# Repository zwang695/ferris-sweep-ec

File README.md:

# Ferris Sweep EC

An open, 34-key (`3x5+2` per half) Topre electrocapacitive split keyboard using
Ferris Sweep-style geometry and the known-built Tako Rev1 sensing architecture.

## Tooling

KiCad 10.0.5 is installed through Flatpak. Use `./scripts/kicad-cli` for
schematic ERC, PCB DRC, exports, and renders. QMK CLI 1.2.0 is also available;
firmware is kept reproducible in this repository rather than depending on the
machine's existing QMK checkout.

This repository is an engineering project. Files under `production/` are not
released for fabrication until every check in `docs/verification-plan.md` has
passed and the release is explicitly tagged as a prototype.

## Revision A goals

- Functional wired electrocapacitive keyboard.
- Separate, non-reversible left and right PCBs.
- 19.05 mm nominal key pitch with Sweep-style column stagger.
- 17 keys per half: three rows of five plus two thumb keys.
- Socketable Pro-Micro-pin-compatible RP2040 controller and local EC sensing
  front end on each half.
- QMK firmware with raw ADC diagnostics for post-assembly threshold tuning.
- USB-C on both halves for flashing and independent bring-up.
- Wired serial split transport.
- No RGB, display, encoder, wireless, or Vial in Revision A.

## Repository layout

- `docs/` — requirements, decisions, reference audit, and verification plan.
- `hardware/` — KiCad project and project-local libraries.
- `mechanical/` — layout coordinates, plate, and compression-stack files.
- `firmware/` — QMK keyboard implementation and keymaps.
- `simulation/` — analog-front-end models and ADC stimulus traces.
- `tests/` — schematic, PCB, firmware, and generated-output checks.
- `references/` — pinned upstream metadata; third-party files retain their
  original licenses and are not copied here until their provenance is clear.
- `production/` — generated Gerbers, drills, BOM, and placement files.

## Status

Controller PCB, Topre plate, bottom plate, and upstream-QMK firmware now pass
the automated pre-fabrication checks. The project remains a prototype: static
checks and behavioral models cannot replace calibration with real domes,
springs, housings, and fabricated sensor electrodes.

Run `./scripts/check-all` for the complete automated gate. See
`docs/tooling.md`, `docs/verification-status.md`, `docs/bom.md`, and
`docs/bring-up.md` for setup, evidence, parts, and physical validation. The
Tako/Cipulot comparison is in `docs/ec-cross-check.md`.

For the wired JLCPCB fabrication and assembly package, run
`./scripts/generate-jlcpcb` and follow `production/jlcpcb/README.md`.

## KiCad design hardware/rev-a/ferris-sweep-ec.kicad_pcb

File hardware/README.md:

# Hardware

`rev-a/` contains the active KiCad 10 design. It starts as a mechanically
imported, renamed copy of the pinned MIT-licensed Tako Rev1 source. The import
is reproducible with `scripts/import-tako-rev1`; subsequent changes are made in
the active source and reviewed against the imported baseline.

The upstream project commit and all other references are pinned in
`references/reference-audit.md`. The original MIT text is retained as
`hardware/LICENSE.tako.MIT`.

The project-level ERC, DRC, firmware, and mechanical gates in
`docs/verification-plan.md` now pass. Revision A is suitable for an informed
prototype review; physical Topre signal margin remains unproven until a real
dome, spring, housing, and fabricated sensor stack are measured.

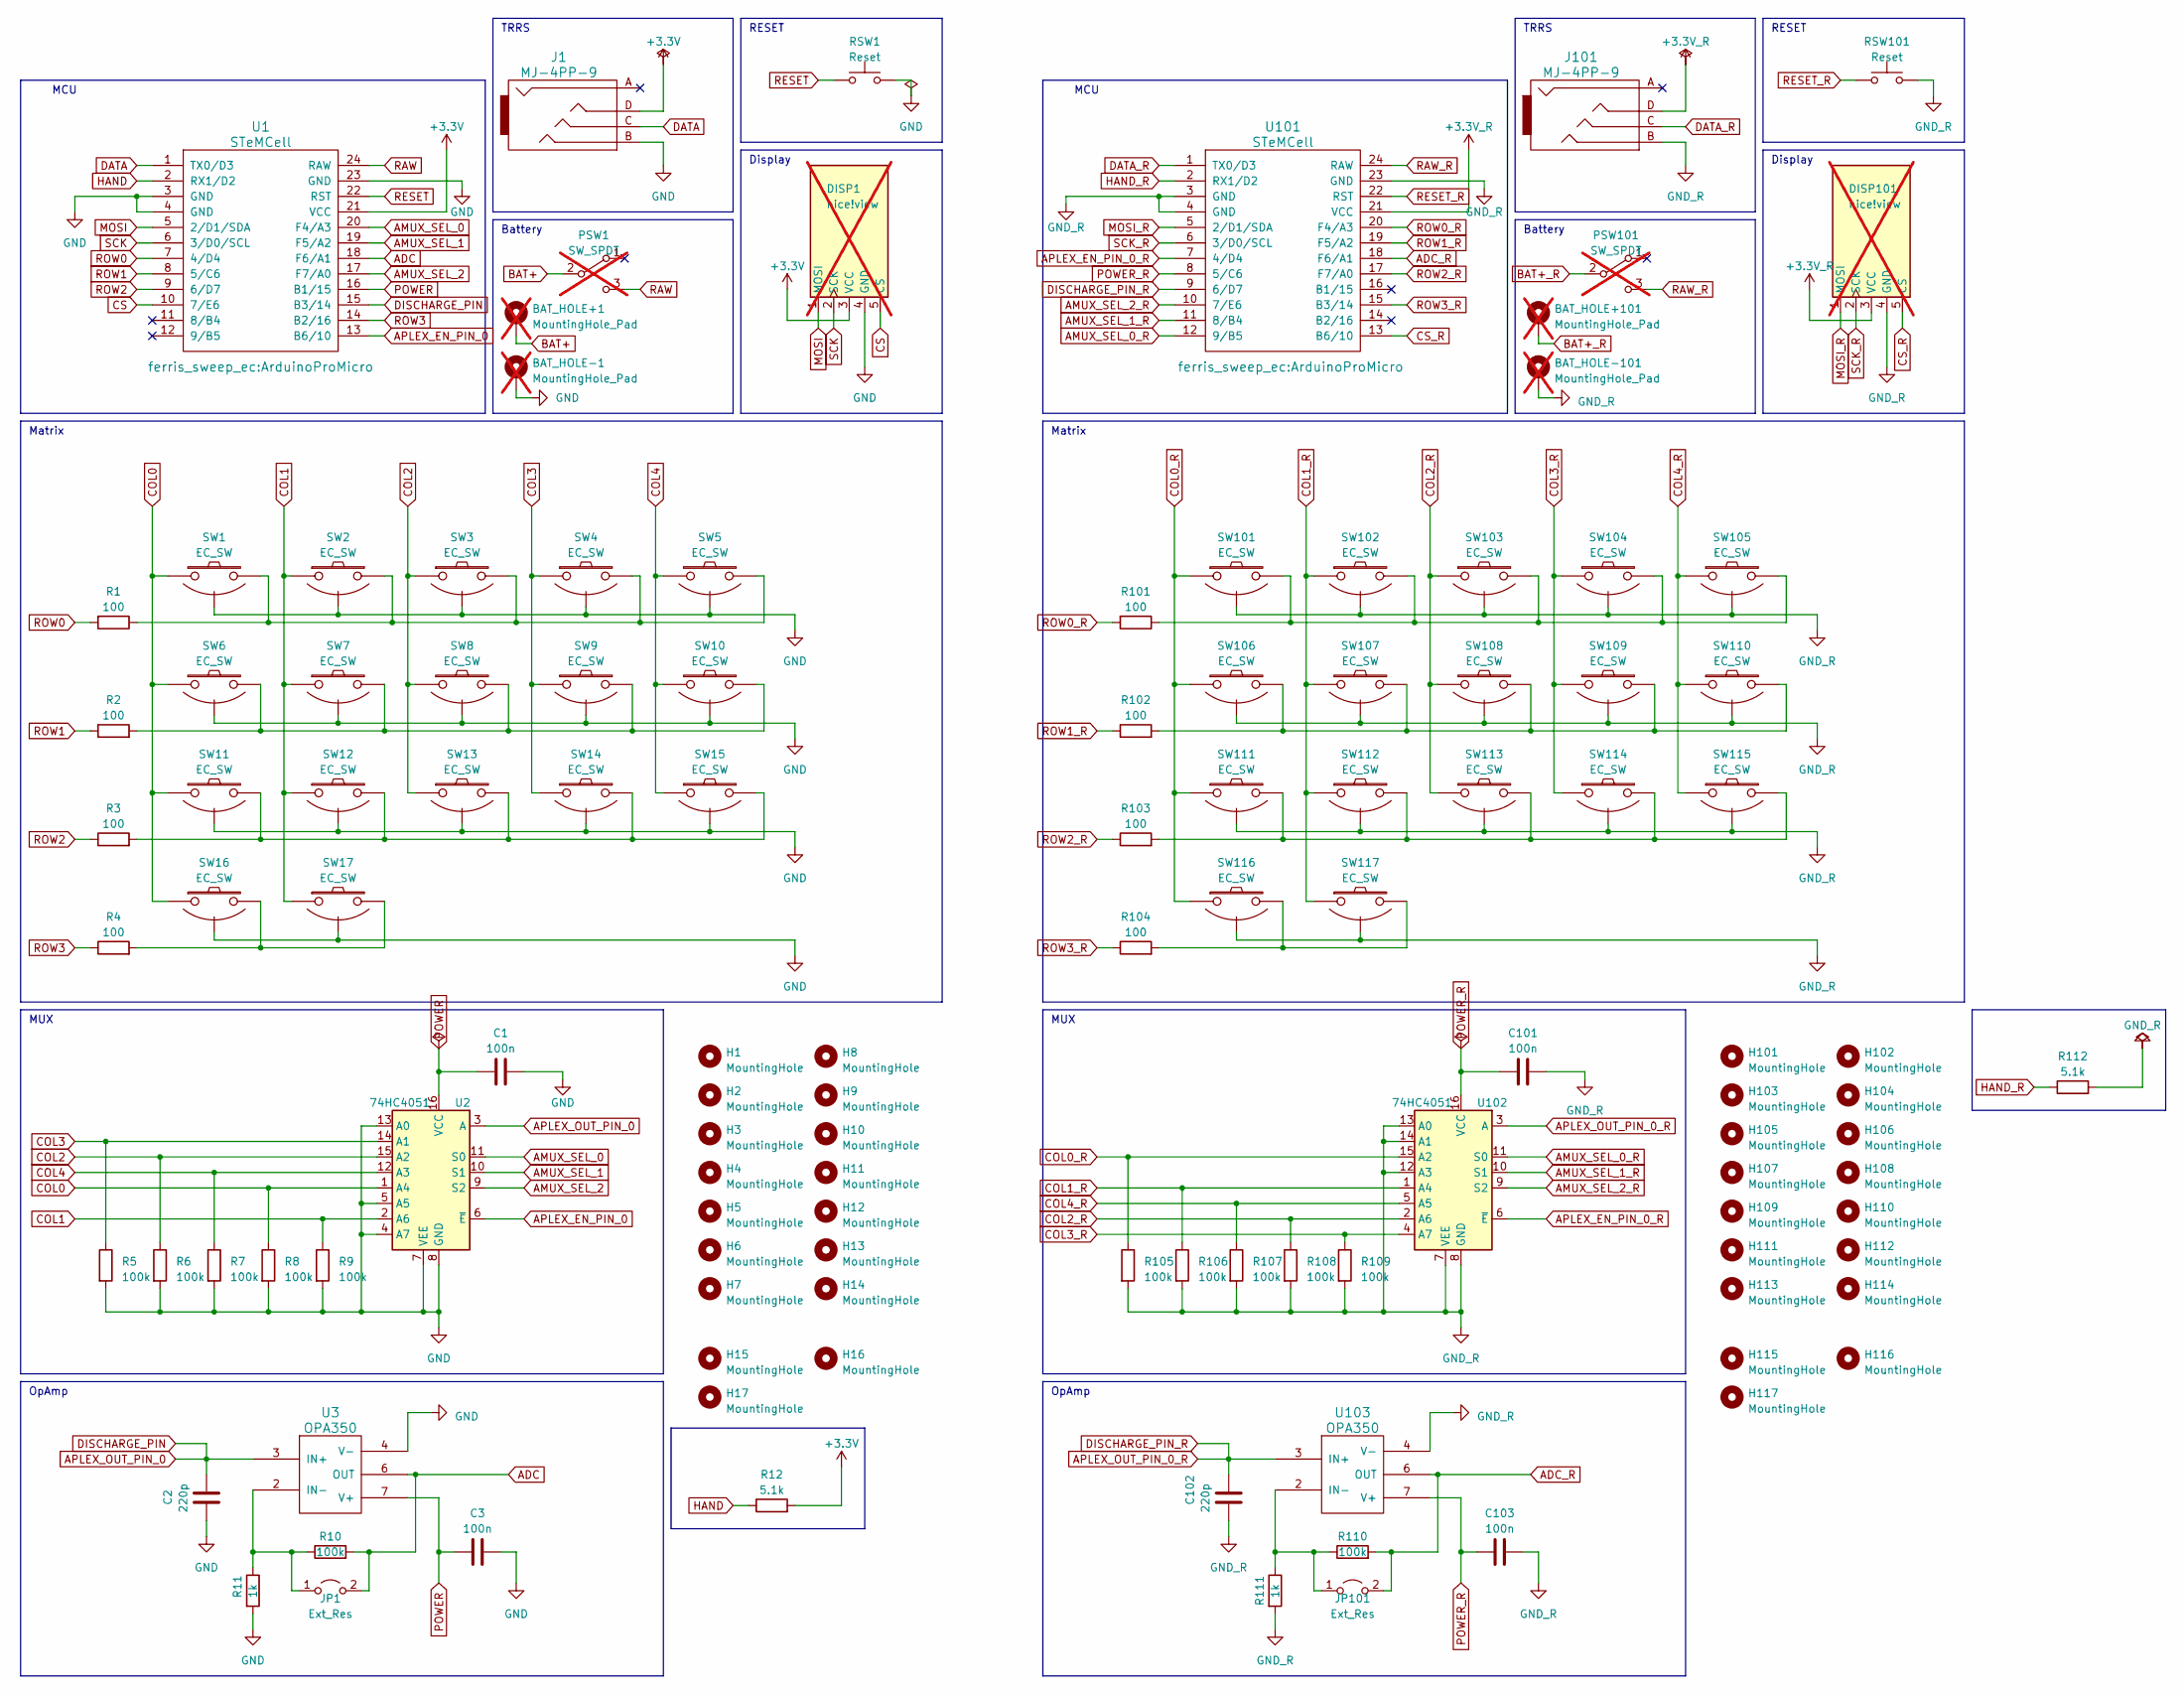
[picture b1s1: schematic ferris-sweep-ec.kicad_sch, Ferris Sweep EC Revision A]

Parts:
BAT_HOLE+1, BAT_HOLE+101: MountingHole_Pad; bat_pin+; not fitted
BAT_HOLE-1, BAT_HOLE-101: MountingHole_Pad; bat_pin-; not fitted
C1, C3, C101, C103: 100n; C_0805_2012Metric_Pad1.18x1.45mm_HandSolder
C2, C102: 220p; C_0805_2012Metric_Pad1.18x1.45mm_HandSolder
DISP1, DISP101: nice!view; nice_view; not fitted
H1, H2, H3, H4, H5, H6, H7, H8, H9, H10, H11, H12, H13, H14, H101, H102, H103, H104, H105, H106, H107, H108, H109, H110, H111, H112, H113, H114: MountingHole; MountingHole_3.4mm
H15, H16, H17, H115, H116, H117: MountingHole; M2_hole_3.5mm
J1, J101: MJ-4PP-9; TRRS-PJ-320A
JP1, JP101: Ext_Res; R_0805_2012Metric_Pad1.20x1.40mm_HandSolder
PSW1, PSW101: SW_SPDT; SW_SPDT_SMD_PCM12; not fitted
R1, R2, R3, R4, R101, R102, R103, R104: 100; R_0805_2012Metric_Pad1.20x1.40mm_HandSolder
R5, R6, R7, R8, R9, R10, R105, R106, R107, R108, R109, R110: 100k; R_0805_2012Metric_Pad1.20x1.40mm_HandSolder
R11, R111: 1k; R_0805_2012Metric_Pad1.20x1.40mm_HandSolder
R12, R112: 5.1k; R_0805_2012Metric_Pad1.20x1.40mm_HandSolder
RSW1, RSW101: Reset; Panasonic_EVQPUL_EVQPUC
SW1, SW2, SW3, SW4, SW5, SW6, SW7, SW8, SW9, SW10, SW11, SW12, SW13, SW14, SW15, SW101, SW102, SW103, SW104, SW105, SW106, SW107, SW108, SW109, SW110, SW111, SW112, SW113, SW114, SW115: EC_SW; ecs_pad_1U_no_ring
SW16, SW17, SW116, SW117: EC_SW; ecs_pad_1U_no_ring_90deg
U1, U101: STeMCell; ArduinoProMicro
U2, U102: 74HC4051; SOIC-16_3.9x9.9mm_P1.27mm
U3, U103: OPA350; SOIC-8_3.9x4.9mm_P1.27mm

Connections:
+3.3V: DISP1.3 (VCC), J1.D, R12.2, U1.21 (VCC)
+3.3V_R: DISP101.3 (VCC), J101.D, U101.21 (VCC)
ADC: JP1.2 (B), R10.2, U1.18 (F6/A1), U3.6 (OUT)
ADC_R: JP101.2 (B), R110.2, U101.18 (F6/A1), U103.6 (OUT)
AMUX_SEL_0: U1.20 (F4/A3), U2.11 (S0)
AMUX_SEL_0_R: U101.12 (9/B5), U102.11 (S0)
AMUX_SEL_1: U1.19 (F5/A2), U2.10 (S1)
AMUX_SEL_1_R: U101.11 (8/B4), U102.10 (S1)
AMUX_SEL_2: U1.17 (F7/A0), U2.9 (S2)
AMUX_SEL_2_R: U101.10 (7/E6), U102.9 (S2)
APLEX_EN_PIN_0: U1.13 (B6/10), U2.6 (~E)
APLEX_EN_PIN_0_R: U101.7 (4/D4), U102.6 (~E)
APLEX_OUT_PIN_0: C2.1, U1.15 (B3/14), U2.3 (A), U3.3 (IN+)
APLEX_OUT_PIN_0_R: C102.1, U101.9 (6/D7), U102.3 (A), U103.3 (IN+)
BAT+: BAT_HOLE+1.1, PSW1.2 (B)
BAT+_R: BAT_HOLE+101.1, PSW101.2 (B)
COL0: R8.1, SW1.1, SW6.1, SW11.1, SW16.1, U2.1 (A4)
COL0_R: R105.1, SW101.1, SW106.1, SW111.1, SW116.1, U102.15 (A2)
COL1: R9.1, SW2.1, SW7.1, SW12.1, SW17.1, U2.2 (A6)
COL1_R: R106.1, SW102.1, SW107.1, SW112.1, SW117.1, U102.1 (A4)
COL2: R6.1, SW3.1, SW8.1, SW13.1, U2.15 (A2)
COL2_R: R108.1, SW103.1, SW108.1, SW113.1, U102.2 (A6)
COL3: R5.1, SW4.1, SW9.1, SW14.1, U2.14 (A1)
COL3_R: R109.1, SW104.1, SW109.1, SW114.1, U102.4 (A7)
COL4: R7.1, SW5.1, SW10.1, SW15.1, U2.12 (A3)
COL4_R: R107.1, SW105.1, SW110.1, SW115.1, U102.5 (A5)
CS: DISP1.5 (CS), U1.10 (7/E6)
CS_R: DISP101.5 (CS), U101.13 (B6/10)
DATA: J1.C, U1.1 (TX0/D3)
DATA_R: J101.C, U101.1 (TX0/D3)
GND: BAT_HOLE-1.1, C1.2, C2.2, C3.2, DISP1.4 (GND), J1.B, R5.2, R6.2, R7.2, R8.2, R9.2, R11.2, RSW1.2, SW1.3 (SG), SW2.3 (SG), SW3.3 (SG), SW4.3 (SG), SW5.3 (SG), SW6.3 (SG), SW7.3 (SG), SW8.3 (SG), SW9.3 (SG), SW10.3 (SG), SW11.3 (SG), SW12.3 (SG), SW13.3 (SG), SW14.3 (SG), SW15.3 (SG), SW16.3 (SG), SW17.3 (SG), U1.3 (GND), U1.4 (GND), U1.23 (GND), U2.4 (A7), U2.5 (A5), U2.7 (VEE), U2.8 (GND), U2.13 (A0), U3.4 (V-)
GND_R: BAT_HOLE-101.1, C101.2, C102.2, C103.2, DISP101.4 (GND), J101.B, R105.2, R106.2, R107.2, R108.2, R109.2, R111.2, R112.2, RSW101.2, SW101.3 (SG), SW102.3 (SG), SW103.3 (SG), SW104.3 (SG), SW105.3 (SG), SW106.3 (SG), SW107.3 (SG), SW108.3 (SG), SW109.3 (SG), SW110.3 (SG), SW111.3 (SG), SW112.3 (SG), SW113.3 (SG), SW114.3 (SG), SW115.3 (SG), SW116.3 (SG), SW117.3 (SG), U101.3 (GND), U101.4 (GND), U101.23 (GND), U102.7 (VEE), U102.8 (GND), U102.12 (A3), U102.13 (A0), U102.14 (A1), U103.4 (V-)
HAND: R12.1, U1.2 (RX1/D2)
HAND_R: R112.1, U101.2 (RX1/D2)
MOSI: DISP1.1 (MOSI), U1.5 (2/D1/SDA)
MOSI_R: DISP101.1 (MOSI), U101.5 (2/D1/SDA)
unnamed: JP1.1 (A), R10.1, R11.1, U3.2 (IN-)
unnamed: JP101.1 (A), R110.1, R111.1, U103.2 (IN-)
unnamed: R1.1, SW1.2, SW2.2, SW3.2, SW4.2, SW5.2
unnamed: R2.2, SW6.2, SW7.2, SW8.2, SW9.2, SW10.2
unnamed: R3.2, SW11.2, SW12.2, SW13.2, SW14.2, SW15.2
unnamed: R4.2, SW16.2, SW17.2
unnamed: R101.1, SW101.2, SW102.2, SW103.2, SW104.2, SW105.2
unnamed: R102.2, SW106.2, SW107.2, SW108.2, SW109.2, SW110.2
unnamed: R103.2, SW111.2, SW112.2, SW113.2, SW114.2, SW115.2
unnamed: R104.2, SW116.2, SW117.2
POWER: C1.1, C3.1, U1.16 (B1/15), U2.16 (VCC), U3.7 (V+)
POWER_R: C101.1, C103.1, U101.8 (5/C6), U102.16 (VCC), U103.7 (V+)
RAW: PSW1.3 (C), U1.24 (RAW)
RAW_R: PSW101.3 (C), U101.24 (RAW)
RESET: RSW1.1, U1.22 (RST)
RESET_R: RSW101.1, U101.22 (RST)
ROW0: R1.2, U1.7 (4/D4)
ROW0_R: R101.2, U101.20 (F4/A3)
ROW1: R2.1, U1.8 (5/C6)
ROW1_R: R102.1, U101.19 (F5/A2)
ROW2: R3.1, U1.9 (6/D7)
ROW2_R: R103.1, U101.17 (F7/A0)
ROW3: R4.1, U1.14 (B2/16)
ROW3_R: R104.1, U101.15 (B3/14)
SCK: DISP1.2 (SCK), U1.6 (3/D0/SCL)
SCK_R: DISP101.2 (SCK), U101.6 (3/D0/SCL)

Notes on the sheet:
Display
OpAmp
MUX
RESET
Matrix
TRRS
Battery
MCU

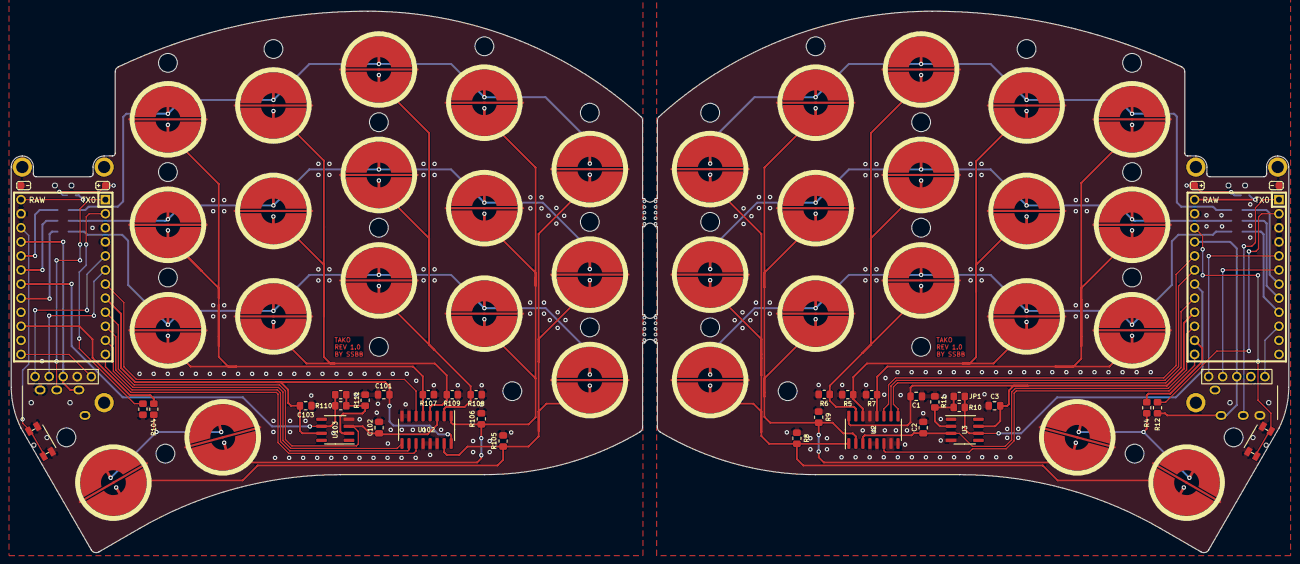
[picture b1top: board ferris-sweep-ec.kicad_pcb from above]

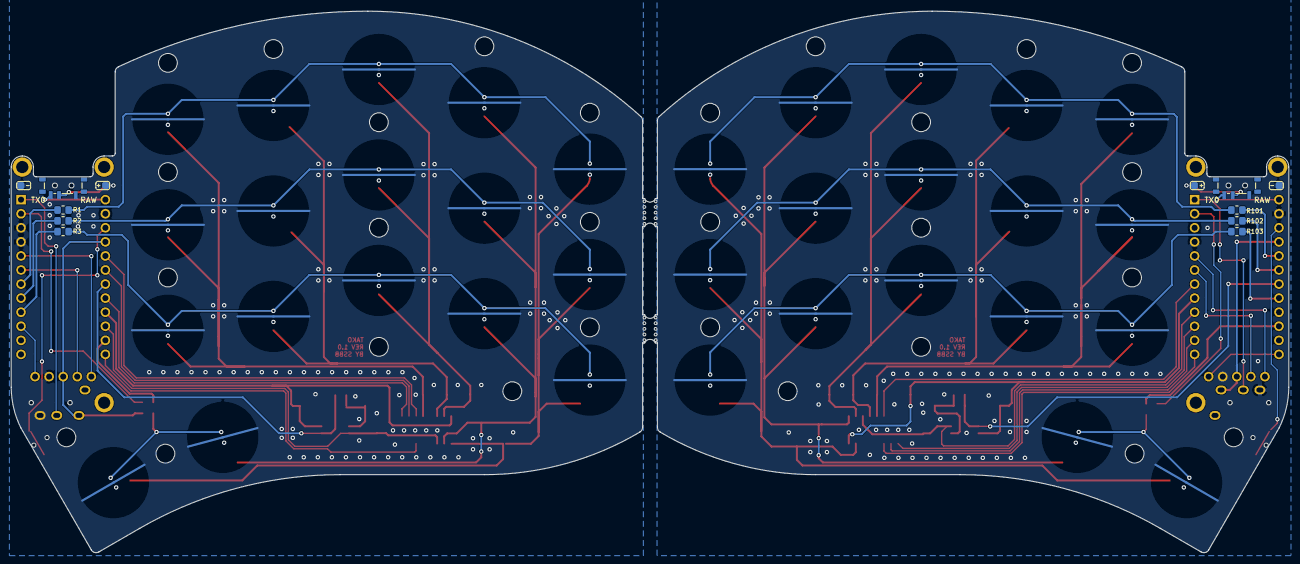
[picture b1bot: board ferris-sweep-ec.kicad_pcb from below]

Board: 2 copper layers, 230.7 x 97.8 mm, 120 parts (10 on the bottom side), 62 nets.

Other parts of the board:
mouse-bite-2mm-slot, mouse-bite-2mm-slot#2: VAL**; mouse-bite-5mm-slot-with-space-for-track
